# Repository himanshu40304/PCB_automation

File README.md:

# PCB Automation & Design Pipeline

An autonomous, end-to-end PCB design, verification, and manufacturing pipeline powered by **KiCad 10**, **SPICE**, **OpenEMS 3D FDTD**, **ParaView**, and **AI-driven Automation Agents**.

⭐ **If you find this repository useful for your PCB workflows or research, please consider giving it a star!**

---

## 🚀 Overview & Automation Architecture

This repository contains automated workflows, design tools, and complete hardware projects demonstrating AI-assisted schematic creation, SPICE verification, electrical rules check (ERC), automated component placement, routing, clearance isolation, and design rules check (DRC).

```mermaid
graph LR
    A["Requirements & Spec"] --> B["Schematic Capture"]
    B --> C["SPICE Simulation & ERC"]
    C --> D["Board Setup & Constraints"]
    D --> E["Component Placement & Floorplanning"]
    E --> F["Routing & Isolated Plane Pours"]
    F --> G["DRC & DFM Production Audit"]
    G --> H["Manufacturing Gerber & BOM Export"]
```

---

## 📂 Projects in this Repository

### 1. `projects/ACtoDCtoMicrocontroller`
* **Description:** An integrated compact IoT board converting mains AC to regulated 5V & 3.3V DC to power an ESP32/Microcontroller with USB programming, switches, and antenna keepout.
* **Key Features:**
  * **Mains AC Input Stage:** Screw terminal (`J1`), NTC inrush limiter (`RT1`), X-Capacitor (`C1`), and HLK-5M05 isolated AC-DC module.
  * **Microcontroller & Logic Domain:** 3.3V LDO regulator, ESP32 module, reset & boot switches, Micro-USB interface, and dedicated RF Antenna Keep-Out Zone.
  * **Physical Isolation:** Strict primary-to-secondary dielectric isolation barrier.
  * **Artifacts:** Complete `.kicad_sch`, `.kicad_pcb`, interactive SVGs, manufacturing BOM, and CPL files.

#### Visual Showcase & 3D Previews

<p align="center">
  <b>Schematic Diagram (Annotated Subsystems)</b><br>
  
</p>

| Top Layer Layout (HV Isolation & 5V Fill) | Bottom Layer Layout (3.3V & Signal Routing) |
| :---: | :---: |
|  |  |

| Top 3D Assembly (HLK Module & AC Protection) | Bottom 3D Assembly (MCU, Buttons, USB) |
| :---: | :---: |
|  |  |

### 2. `projects/AC_DC_converter_with_regulated_dc`
* **Description:** A **$60\text{ mm} \times 50\text{ mm}$** AC-to-DC Adjustable Regulated Power Supply using a Full-Wave Bridge Rectifier and LM317.
* **Key Features:**
  * **Primary High-Voltage AC Domain ($X \le 120\text{ mm}$):** 2-pin screw terminal (`J1`), MOV surge suppressor (`RV_MOV1`), 5x20mm fuse (`F1`), and 1N4007 bridge rectifier (`D1–D4`).
  * **Secondary Low-Voltage DC Domain ($X \ge 122\text{ mm}$):** $1000\mu\text{F}$ bulk filter (`C1`), LM317 regulator (`U1`), 5k$\Omega$ precision trimpot (`RV1`), output decoupling (`C4`, `C5`), and green LED indicator (`D7`).
  * **Safety & Isolation:** $>3.0\text{ mm}$ physical creepage/clearance barrier between Primary AC and Secondary DC.
  * **Isolated Ground Pours:** Top and Bottom GND copper pours restricted to the DC secondary domain.
  * **Verification Status:** **0 ERC Errors, 0 DRC Errors, 0 Courtyard Overlaps, 0 Boundary Violations**.

#### Visual Showcase & Design Views

| Schematic (Annotated Sections) | 2D PCB Layout (HV/LV Split & GND Pour) |
| :---: | :---: |
|  |  |

<p align="center">
  <b>3D Board Assembly Render</b><br>
  
</p>

### 3. `projects/Binary_Counter_8Bit`
* **Description:** An autonomous 8-Bit Binary Counter circuit ($0 - 255$) featuring an NE555 timer clock generator, 74HC590 8-bit binary counter, 8-LED binary readout bar, speed trimpot, and USB power.
* **Key Features:**
  * **USB-B Micro 5V Input:** Over-current fuse protection (`F1`), Schottky reverse diode (`D1`), and SMAJ5.0A TVS protection (`D2`).
  * **NE555 Precision Clock Generator:** Astable timer circuit with adjustable speed potentiometer (`RV1`) and clock pulse LED indicator (`D_CLK`).
  * **74HC590 8-Bit Binary Counter & Register:** Direct driving of an 8-LED binary output array (`D3 - D10`) with dedicated current limiting resistors (`R3 - R10`).
  * **Active Reset Circuit:** Tactile pushbutton (`SW_RST`) with pull-up resistor (`R_PULL_RST`).

#### Visual Showcase & 3D Previews

<p align="center">
  <b>Schematic Diagram (Timer, Counter & Output Display)</b><br>
  
</p>

| 2D PCB Layout (Floorplan & Traces) | 2D PCB Layout (Copper & Pour View) |
| :---: | :---: |
|  |  |

<p align="center">
  <b>3D Board Assembly Render</b><br>
  
</p>

### 4. `projects/RF_Detector`
* **Description:** A 4-Layer High-Frequency RF Logarithmic Power Detector board ($500\text{ MHz} - 1.0\text{ GHz}$) featuring an SMA edge input, Analog Devices AD8313 logarithmic detector, ADS7042 12-bit SPI ADC, and dedicated analog/digital ground splits.
* **Key Features:**
  * **RF Signal Path:** $50\ \Omega$ microstrip line ($w = 0.38\text{ mm}$) on $0.2\text{ mm}$ FR4 core directly referencing a solid Layer 2 ground plane.
  * **Full-Wave 3D FDTD EM Simulation (OpenEMS):** $S_{11} = -15.96\text{ dB}$ resonance at $750\text{ MHz}$, $-29.66\text{ dB}$ max crosstalk isolation into the adjacent digital SPI bus.
  * **3D Field Visualization (ParaView):** Time-domain wave propagation ($\vec{E}(t)$) and frequency-domain harmonic vector distributions exported as VTK field dumps.

### 5. `projects/RF_LVDS/LVDS` (High-Speed $\ge 400\text{ Mbps}$ Differential Link)
* **Description:** A 4-Layer High-Speed LVDS Evaluation Board featuring **TI SN65LVDS1D (Driver)** and **SN65LVDT2D (Receiver with internal 110 Ω termination)**.
* **Key Features:**
  * **Controlled Impedance Interconnects:** $100\ \Omega$ edge-coupled microstrip ($W = 0.15\text{ mm}, S = 0.15\text{ mm}$) over $0.1\text{ mm}$ prepreg, with $50\ \Omega$ single-ended RF SMA launches.
  * **Ground Integrity & Via Stitching:** 5.0 mm uniform ground stitching grid across the board interior with a perimeter via fence for low-inductance return loops.
  * **3D Full-Wave EM Co-Simulation:** Full FDTD wave propagation ($E$-field, $H$-field, and $J$-current density) animated in ParaView.
  * **Manufacturing:** Complete Gerber RS-274X, NC Drill, and 3D STEP models with 0 DRC violations and 0 unconnected pads.

---

## 🛠️ Automated Tools & Pipeline Frameworks

* **`PCB_AUTOMATION_PIPELINE_GUIDE.md`**: Complete architectural reference guide for automating KiCad schematic capture, layout, SPICE simulation, OpenEMS 3D EM analysis, and Gerber generation.
* **`pcb-workflow.md`**: Step-by-step workflow with mandatory pre-layout SPICE and post-layout OpenEMS verification gates.
* **`KiCAD-MCP-Server`**: Model Context Protocol integration enabling autonomous LLM interaction with KiCad's layout engine.
* **`SPICEBridge` (`kicad-spice`)**: Automated SPICE netlist extraction and ngspice simulation harness.
* **`openems-sim` (`antenna-cad`)**: 3D Full-Wave FDTD Electromagnetic field solver running inside a dedicated Docker container (`antenna-cad-openems`).
* **`ParaView 6.1.1`**: 3D scientific field viewer for near-field coupling, surface currents, and wave propagation animation.
* **`Saturn PCB Toolkit`**: Deterministic analytical transmission line, via capacitance, and thermal modeling toolkit.
* **`Konnect`**: Automated net connectivity and routing optimization toolset.

---

## 🤝 Commercial Inquiries & Custom PCB Design

Need custom hardware design, high-speed differential layout, RF / antenna 3D EM simulation, or pre-fabrication DRC/SPICE auditing?
- Open an issue or start a [GitHub Discussion](https://github.com/himanshu40304/PCB_automation/discussions).
- Turnaround time for SPICE-verified, DRC-clean design packages is typically **under 24–48 hours**.

---

## 📄 License

This project is licensed under the **MIT License** - see the [LICENSE](LICENSE) file for details. Free for both open-source and commercial applications.

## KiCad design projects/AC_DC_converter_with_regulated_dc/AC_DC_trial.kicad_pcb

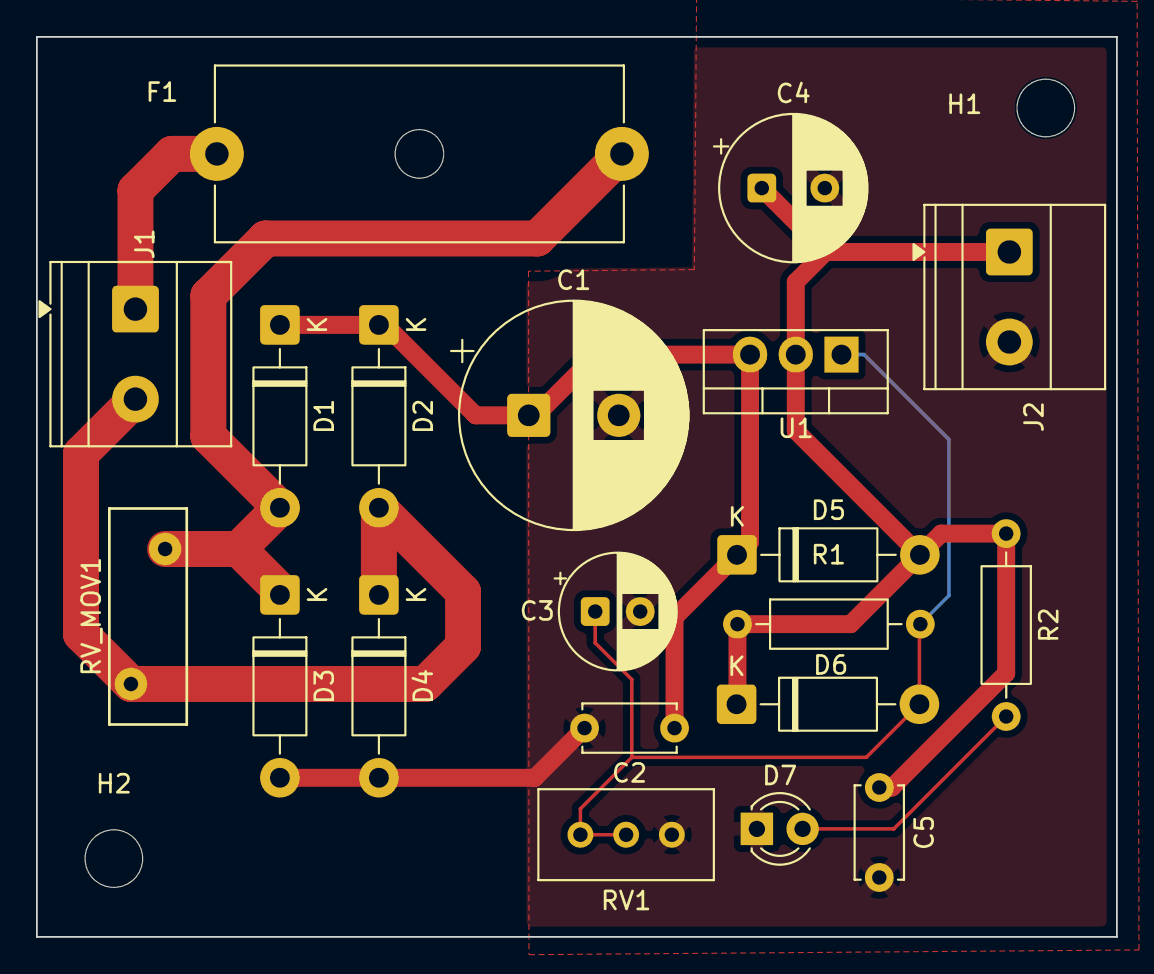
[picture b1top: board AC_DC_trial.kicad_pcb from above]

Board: 4 copper layers, 60.0 x 50.0 mm, 22 parts (0 on the bottom side), 8 nets.

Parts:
C1: 1000uF_50V; CP_Radial_D12.5mm_P5.00mm
C2, C5: 100nF; C_Disc_D5.0mm_W2.5mm_P5.00mm
C3: 10uF_50V; CP_Radial_D6.3mm_P2.50mm
C4: 100uF_50V; CP_Radial_D8.0mm_P3.50mm
D1, D2, D3, D4, D5, D6: 1N4007; D_DO-41_SOD81_P10.16mm_Horizontal
D7: Green_LED; LED_D3.0mm
F1: 1A_250V; Fuseholder_Cylinder-5x20mm_Schurter_0031_8201_Horizontal_Op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
H1, H2: MountingHole_M3; MountingHole_3.2mm_M3
J1: AC_IN; TerminalBlock_Phoenix_MKDS-1,5-2_1x02_P5.00mm_Horizontal
J2: DC_OUT; TerminalBlock_Phoenix_MKDS-1,5-2_1x02_P5.00mm_Horizontal
R1: 240R; R_Axial_DIN0207_L6.3mm_D2.5mm_P10.16mm_Horizontal
R2: 2.2k; R_Axial_DIN0207_L6.3mm_D2.5mm_P10.16mm_Horizontal
RV1: 5k; Potentiometer_Bourns_3296W_Vertical
RV_MOV1: MOV_14D; RV_Disc_D12mm_W4.3mm_P7.5mm
U1: LM317T; TO-220-3_Vertical

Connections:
AC_IN1: F1.1, J1.1
AC_L: D1.2 (A), D3.1 (K), F1.2, RV_MOV1.1
AC_N: D2.2 (A), D4.1 (K), J1.2, RV_MOV1.2
ADJ_NODE: C3.1, D6.2 (A), R1.2, RV1.1, RV1.2, U1.1 (ADJ)
GND: C1.2, C2.2, C3.2, C4.2, C5.2, D3.2 (A), D4.2 (A), D7.1 (K), J2.2, RV1.3
LED_A: D7.2 (A), R2.2
VOUT: C4.1, C5.1, D5.2 (A), D6.1 (K), J2.1, R1.1, R2.1, U1.2 (VO)
VRECT_POS: C1.1, C2.1, D1.1 (K), D2.1 (K), D5.1 (K), U1.3 (VI)

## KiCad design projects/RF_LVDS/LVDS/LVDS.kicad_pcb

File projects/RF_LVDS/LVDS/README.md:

# High-Speed Point-to-Point LVDS Test & Evaluation PCB

A high-speed 4-layer Low-Voltage Differential Signaling (LVDS) evaluation board featuring the **Texas Instruments SN65LVDS1D (Driver)** and **SN65LVDT2D (Receiver with integrated 110 Ω termination)** capable of $\ge 400\text{ Mbps}$ data transmission with co-planar controlled-impedance interconnects, full-coverage ground stitching, and 3D full-wave OpenEMS/ParaView simulation.

---

## 📐 Board Specifications

| Parameter | Specification | Notes |
| :--- | :--- | :--- |
| **Dimensions** | 70.0 mm × 50.0 mm | Standard compact evaluation form factor |
| **Layer Stackup** | 4-Layer Controlled Impedance (JEDEC standard) | $1.6\text{ mm}$ overall thickness, FR4 ($\varepsilon_r = 4.5$) |
| **Layer 1 (Top)** | High-Speed Microstrip + RF SMA Launch | $100\ \Omega$ diff pair ($W=0.15\text{ mm}, S=0.15\text{ mm}$), $50\ \Omega$ single-ended ($W=0.18\text{ mm}$) |
| **Layer 2 (Inner 1)** | Solid Unbroken GND Ground Plane | Continuous reference plane directly under high-speed traces |
| **Layer 3 (Inner 2)** | 3.3V Power Plane (PDN) | Low-impedance power distribution with 100 nF + 1 nF decoupling |
| **Layer 4 (Bottom)** | Solid GND Shield Plane | Ground return reference plane |
| **Via Stitching** | 5.0 mm Interior Grid + 3.5 mm Perimeter Fence | 0.6 mm pad diameter, 0.3 mm drill hole for low-inductance return paths |

---

## ⚡ Circuit Architecture

```mermaid
graph LR
    SMA1["J1: Input SMA (50 Ω)"] -->|"Single-Ended 50 Ω"| U2["TI SN65LVDS1D (Driver)"]
    U2 -->|"/LVDS_P (100 Ω Diff)"| U3["TI SN65LVDT2D (Receiver)"]
    U2 -->|"/LVDS_N (100 Ω Diff)"| U3
    U3 -->|"Single-Ended 50 Ω"| SMA2["J2: Output SMA (50 Ω)"]
    PWR["J3: 3.3V Power Header"] --> DEC["Decoupling (10uF + 100nF + 1nF)"]
    DEC --> U2
    DEC --> U3
```

---

## 🔬 3D Full-Wave Electromagnetic & Field Simulation Pipeline

High-speed PCB signals at $> 400\text{ Mbps}$ are **guided electromagnetic waves**, where energy travels primarily through the dielectric substrate between the signal trace and reference ground plane. 

To validate transmission line dynamics before physical fabrication, this board was simulated using **OpenEMS (Finite-Difference Time-Domain full-wave Maxwell solver)** and visualized in **ParaView 6.1**:

```mermaid
graph LR
    A["KiCad Layout & Stackup"] --> B["OpenEMS 3D FDTD Engine"]
    B --> C["Full-Wave Maxwell Solution (E, H, J fields)"]
    C --> D["ParaView 3D Vector & Surface LIC Analysis"]
```

### Key Simulation Models:
1. **End-to-End Transmission Line Domain (70 mm × 50 mm)**:
   - Full board substrate modeled in FR4 ($\varepsilon_r = 4.5, \tan\delta = 0.02$) over a $0.10\text{ mm}$ prepreg height to Layer 2 solid ground plane.
   - Left SMA input launch ($50\ \Omega$) $\rightarrow$ Driver `U2` $\rightarrow$ $100\ \Omega$ Differential Pair ($W=0.15\text{ mm}, S=0.15\text{ mm}$) $\rightarrow$ Receiver `U3` ($110\ \Omega$ termination) $\rightarrow$ Right SMA output launch ($50\ \Omega$).
2. **Surface LIC (Line Integral Convolution) Vector Field Analysis**:
   - Computes continuous streamflow streaklines directly from the electric vector field $\vec{E}(t)$, revealing:
     - **Radial Launch Pattern**: Coaxial TEM-to-microstrip transition at the SMA connector launch.
     - **Differential Coupling**: Strong transverse field confinement tightly bounded between the positive and negative differential microstrips.
     - **Zero Stray Coupling**: Near-zero field leakage into surrounding ground fill.
3. **Ground Plane Integrity & Perimeter Via Shielding**:
   - High-density ground via stitching matrix (5.0 mm grid) connecting Top, Inner 1, and Bottom ground planes, backed by a perimeter via fence to suppress edge radiation and maintain low-inductance ground return loops.

---

## 🌟 Engineering Benefits of 3D EM Simulation for High-Speed PCBs

| Engineering Challenge | How 3D EM Simulation Resolves It |
| :--- | :--- |
| **Impedance Discontinuities** | Visualizes localized wave reflections and capacitance bumps at SMA launches and chip pad transitions before tape-out. |
| **Differential Symmetry & Skew** | Verifies equal phase velocity and tight coupling between `/LVDS_P` and `/LVDS_N`, preventing common-mode noise conversion. |
| **High-Frequency Return Currents** | Proves that the high-frequency return current stays tightly confined on Layer 2 GND directly beneath the trace path, minimizing loop inductance. |
| **EMI & Edge Radiation Suppression** | Validates that the solid ground reference planes and perimeter stitching fence prevent fringing electromagnetic waves from radiating off the PCB edges. |
| **Pre-Fabrication Signoff** | Eliminates costly PCB prototype respins by diagnosing signal integrity (SI) and electromagnetic compatibility (EMC) bottlenecks in software. |

---

## 📁 Manufacturing Artifacts
- **Gerber RS-274X Package:** `gerber/`
- **Excellon NC Drill:** `gerber/LVDS.drl`
- **3D Mechanical STEP Model:** `LVDS.step`
- **DRC & ERC Status:** **Passed (0 DRC Violations, 0 Unconnected Items)**.

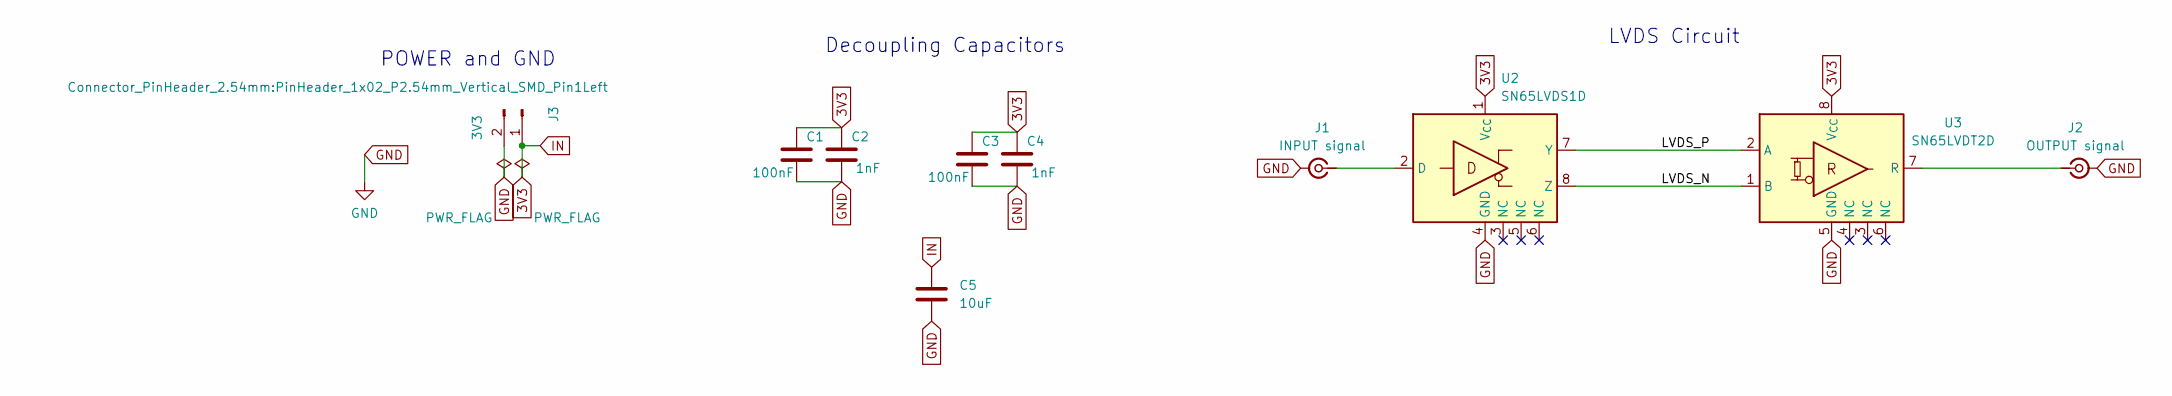
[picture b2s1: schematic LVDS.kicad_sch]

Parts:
C1, C3: 100nF; C_0805_2012Metric
C2, C4: 1nF; C_0805_2012Metric
C5: 10uF; C_0805_2012Metric
J1: INPUT signal; SMA_Amphenol_132134-10_Vertical
J2: OUTPUT signal; SMA_Amphenol_132134-10_Vertical
J3: 3V3; PinHeader_1x02_P2.54mm_Vertical_SMD_Pin1Left
U2: SN65LVDS1D; SOIC-8_3.9x4.9mm_P1.27mm
U3: SN65LVDT2D; SOIC-8_3.9x4.9mm_P1.27mm

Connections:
3V3: C1.1, C2.1, C3.1, C4.1, C5.1, J3.1, U2.1 (V_{CC}), U3.8 (V_{CC})
/LVDS_N: U2.8 (Z), U3.1 (B)
/LVDS_P: U2.7 (Y), U3.2 (A)
GND: C1.2, C2.2, C3.2, C4.2, C5.2, J1.2 (Ext), J2.2 (Ext), J3.2, U2.4 (GND), U3.5 (GND)
unnamed: J1.1 (In), U2.2 (D)
unnamed: J2.1 (In), U3.7 (R)

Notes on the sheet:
LVDS Circuit
Decoupling Capacitors
POWER and GND

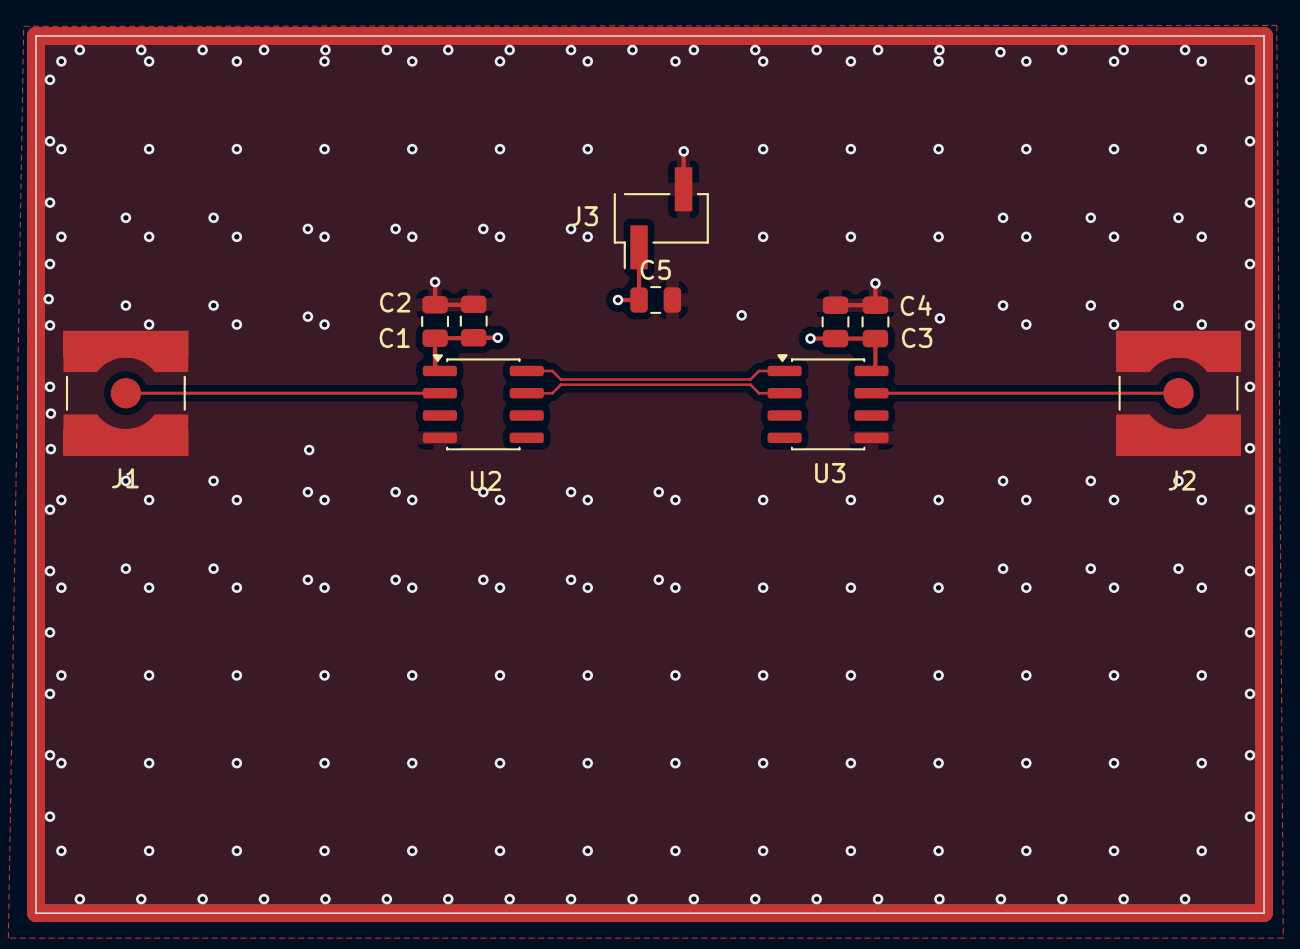
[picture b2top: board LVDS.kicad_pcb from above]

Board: 4 copper layers, 70.0 x 50.0 mm, 10 parts (0 on the bottom side), 6 nets.

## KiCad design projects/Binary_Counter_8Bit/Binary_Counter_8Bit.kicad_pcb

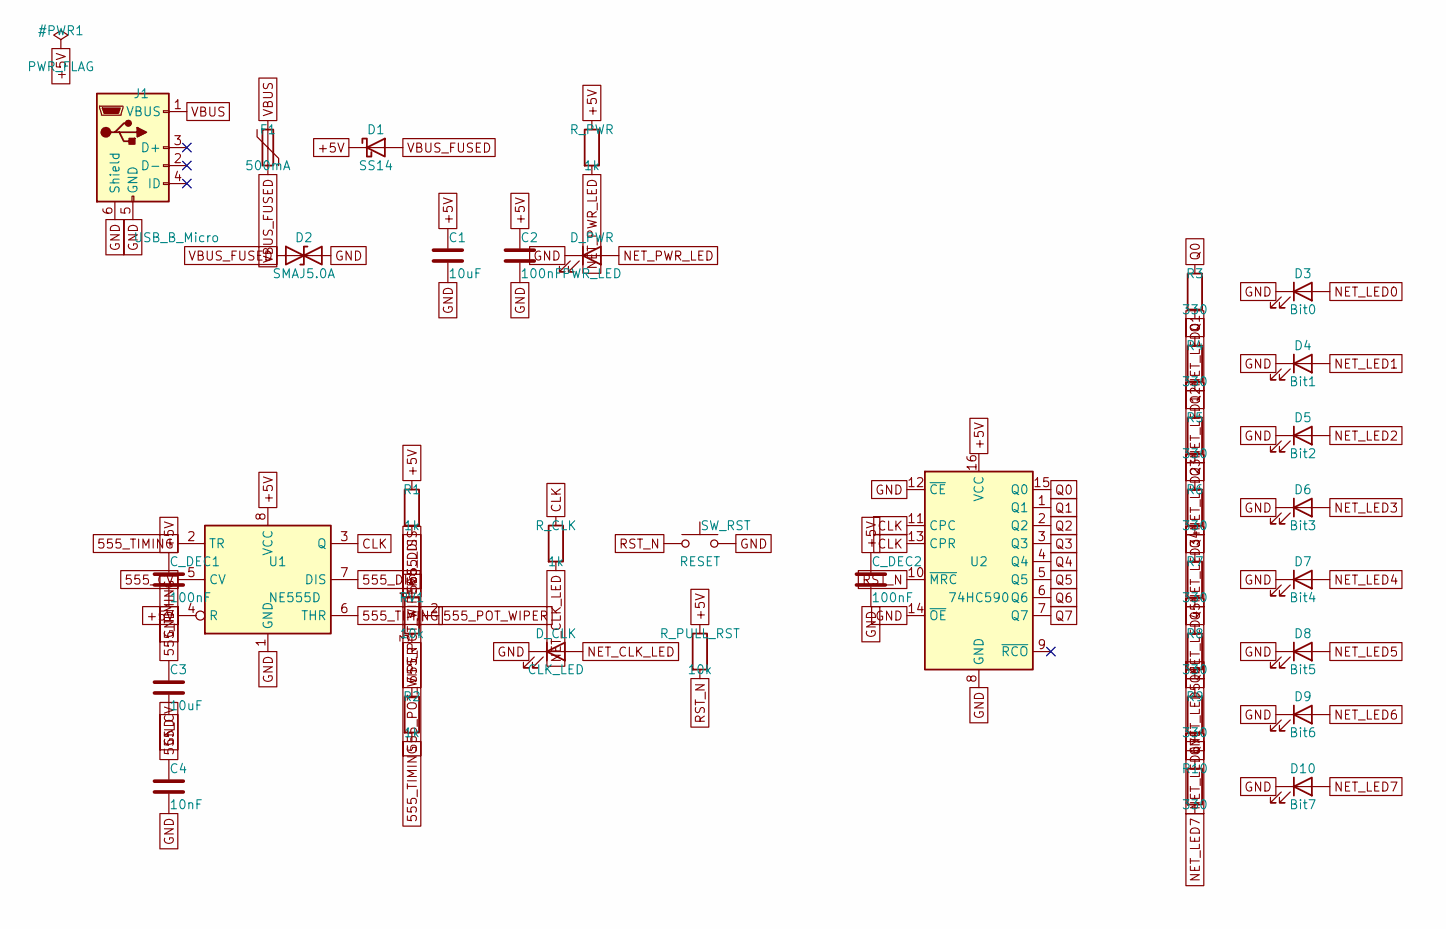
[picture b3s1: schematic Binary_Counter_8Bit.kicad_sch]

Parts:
C1, C3: 10uF; C_1206_3216Metric
C2: 100nF; C_0805_2012Metric
C4: 10nF; C_0805_2012Metric
C_DEC1, C_DEC2: 100nF; C_0805_2012Metric
D1: SS14; D_SMA
D2: SMAJ5.0A; D_SMA
D3: Bit0; LED_0805_2012Metric
D4: Bit1; LED_0805_2012Metric
D5: Bit2; LED_0805_2012Metric
D6: Bit3; LED_0805_2012Metric
D7: Bit4; LED_0805_2012Metric
D8: Bit5; LED_0805_2012Metric
D9: Bit6; LED_0805_2012Metric
D10: Bit7; LED_0805_2012Metric
D_CLK: CLK_LED; LED_0805_2012Metric
D_PWR: PWR_LED; LED_0805_2012Metric
F1: 500mA; Fuse_1206_3216Metric
J1: USB_B_Micro; USB_Micro-B_Molex_47346-0001
R1, R2: 1k; R_0805_2012Metric
R3, R4, R5, R6, R7, R8, R9, R10: 330; R_0805_2012Metric
RV1: 10k; Potentiometer_Bourns_3386P_Vertical
R_CLK: 1k; R_0805_2012Metric
R_PULL_RST: 10k; R_0805_2012Metric
R_PWR: 1k; R_0805_2012Metric
SW_RST: RESET; SW_SPST_PTS645Sx43SMTR92
U1: NE555D; SOIC-8_3.9x4.9mm_P1.27mm
U2: 74HC590; SOIC-16_3.9x9.9mm_P1.27mm

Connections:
555_CV: C4.1, U1.5 (CV)
555_DIS: R1.2, RV1.1, U1.7 (DIS)
555_POT_WIPER: R2.1, RV1.2, RV1.3
555_TIMING: C3.1, R2.2, U1.2 (TR), U1.6 (THR)
+5V: C1.1, C2.1, C_DEC1.1, C_DEC2.1, D1.1 (K), R1.1, R_PULL_RST.1, R_PWR.1, U1.4 (R), U1.8 (VCC), U2.16 (VCC)
CLK: R_CLK.1, U1.3 (Q), U2.11 (CPC), U2.13 (CPR)
GND: C1.2, C2.2, C3.2, C4.2, C_DEC1.2, C_DEC2.2, D2.2 (A2), D3.1 (K), D4.1 (K), D5.1 (K), D6.1 (K), D7.1 (K), D8.1 (K), D9.1 (K), D10.1 (K), D_CLK.1 (K), D_PWR.1 (K), J1.5 (GND), J1.6 (Shield), SW_RST.2, U1.1 (GND), U2.8 (GND), U2.12 (~CE), U2.14 (~OE)
NET_CLK_LED: D_CLK.2 (A), R_CLK.2
NET_LED0: D3.2 (A), R3.2
NET_LED1: D4.2 (A), R4.2
NET_LED2: D5.2 (A), R5.2
NET_LED3: D6.2 (A), R6.2
NET_LED4: D7.2 (A), R7.2
NET_LED5: D8.2 (A), R8.2
NET_LED6: D9.2 (A), R9.2
NET_LED7: D10.2 (A), R10.2
NET_PWR_LED: D_PWR.2 (A), R_PWR.2
Q0: R3.1, U2.15 (Q0)
Q1: R4.1, U2.1 (Q1)
Q2: R5.1, U2.2 (Q2)
Q3: R6.1, U2.3 (Q3)
Q4: R7.1, U2.4 (Q4)
Q5: R8.1, U2.5 (Q5)
Q6: R9.1, U2.6 (Q6)
Q7: R10.1, U2.7 (Q7)
RST_N: R_PULL_RST.2, SW_RST.1, U2.10 (~MRC)
VBUS: F1.1, J1.1 (VBUS)
VBUS_FUSED: D1.2 (A), D2.1 (A1), F1.2

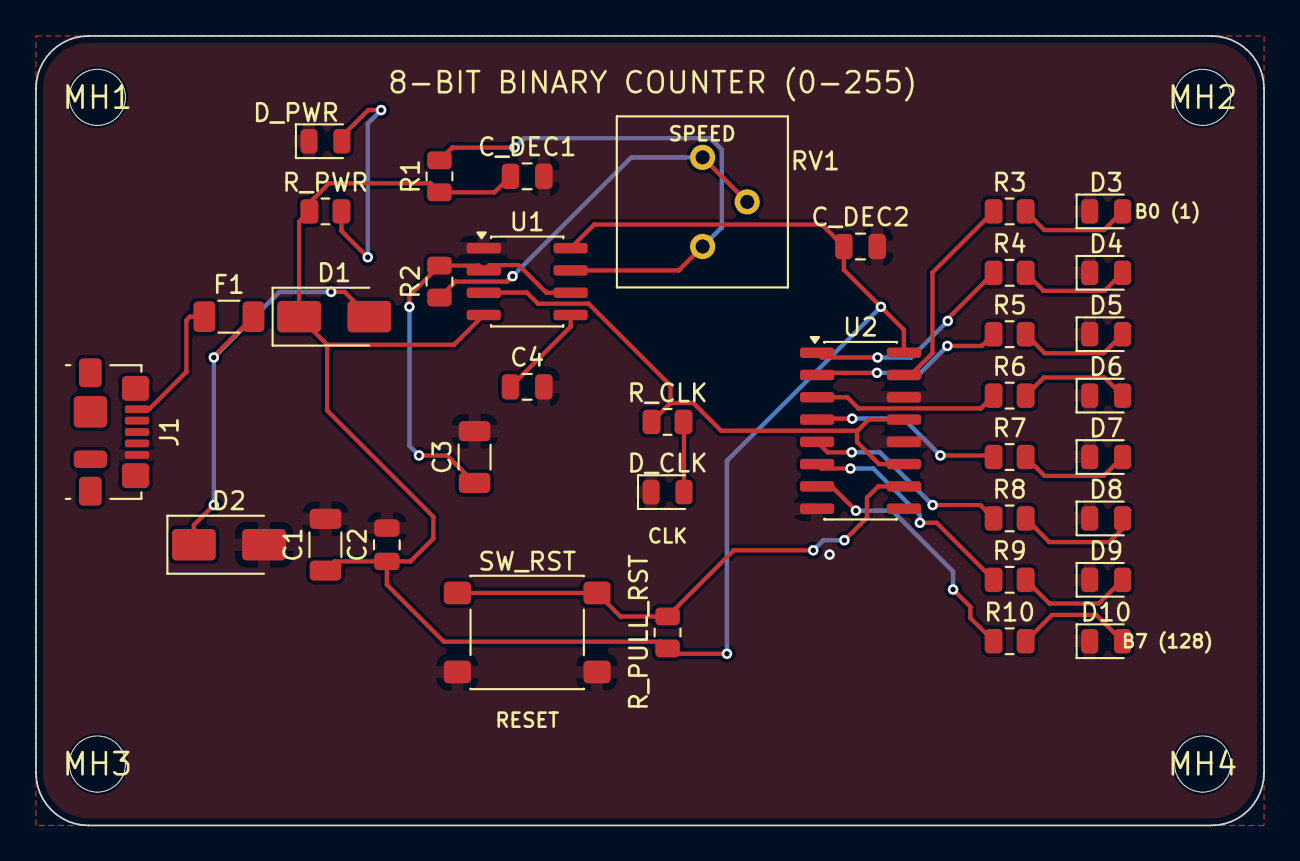
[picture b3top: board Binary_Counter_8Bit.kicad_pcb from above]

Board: 2 copper layers, 70.0 x 45.0 mm, 41 parts (0 on the bottom side), 28 nets.

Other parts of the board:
MH1, MH2, MH3, MH4: MountingHole_3.2mm

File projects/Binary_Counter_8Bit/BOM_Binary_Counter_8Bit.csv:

value,footprint,quantity,references
MountingHole_3.2mm,MountingHole:MountingHole_3.2mm,4,"['MH4', 'MH3', 'MH2', 'MH1']"
USB_B_Micro,Connector_USB:USB_Micro-B_Molex_47346-0001,1,['J1']
330,Resistor_SMD:R_0805_2012Metric,8,"['R7', 'R4', 'R3', 'R8', 'R9', 'R5', 'R6', 'R10']"
SMAJ5.0A,Diode_SMD:D_SMA,1,['D2']
10k,Potentiometer_THT:Potentiometer_Bourns_3386P_Vertical,1,['RV1']
10uF,Capacitor_SMD:C_1206_3216Metric,2,"['C3', 'C1']"
Bit2,LED_SMD:LED_0805_2012Metric,1,['D5']
10nF,Capacitor_SMD:C_0805_2012Metric,1,['C4']
1k,Resistor_SMD:R_0805_2012Metric,4,"['R1', 'R2', 'R_PWR', 'R_CLK']"
RESET,Button_Switch_SMD:SW_SPST_PTS645Sx43SMTR92,1,['SW_RST']
Bit4,LED_SMD:LED_0805_2012Metric,1,['D7']
Bit6,LED_SMD:LED_0805_2012Metric,1,['D9']
Bit1,LED_SMD:LED_0805_2012Metric,1,['D4']
PWR_LED,LED_SMD:LED_0805_2012Metric,1,['D_PWR']
NE555D,Package_SO:SOIC-8_3.9x4.9mm_P1.27mm,1,['U1']
Bit5,LED_SMD:LED_0805_2012Metric,1,['D8']
500mA,Fuse:Fuse_1206_3216Metric,1,['F1']
10k,Resistor_SMD:R_0805_2012Metric,1,['R_PULL_RST']
CLK_LED,LED_SMD:LED_0805_2012Metric,1,['D_CLK']
Bit3,LED_SMD:LED_0805_2012Metric,1,['D6']
100nF,Capacitor_SMD:C_0805_2012Metric,3,"['C2', 'C_DEC2', 'C_DEC1']"
SS14,Diode_SMD:D_SMA,1,['D1']
74HC590,Package_SO:SOIC-16_3.9x9.9mm_P1.27mm,1,['U2']
Bit0,LED_SMD:LED_0805_2012Metric,1,['D3']
Bit7,LED_SMD:LED_0805_2012Metric,1,['D10']

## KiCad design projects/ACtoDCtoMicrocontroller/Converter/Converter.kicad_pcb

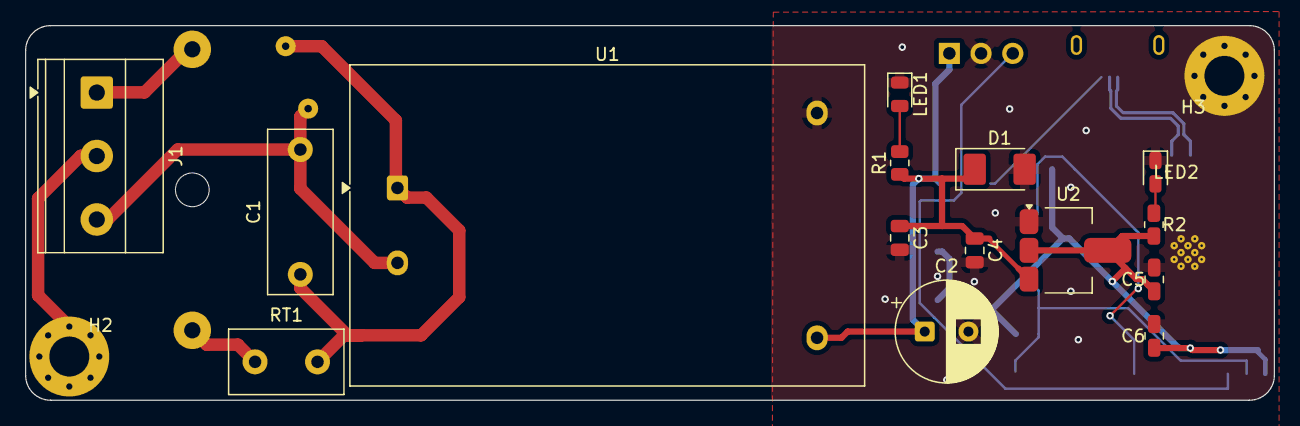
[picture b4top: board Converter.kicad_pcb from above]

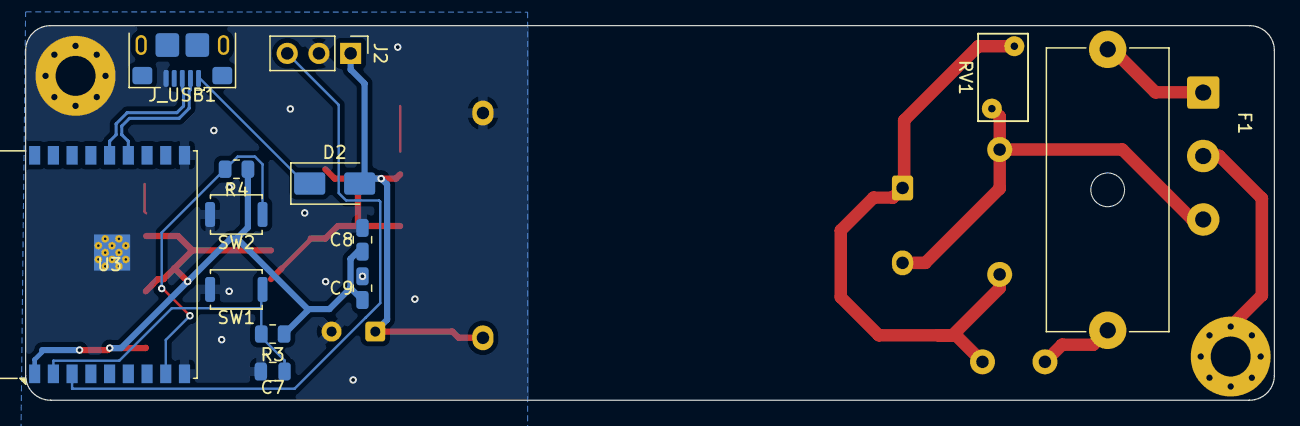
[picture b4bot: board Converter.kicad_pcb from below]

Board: 2 copper layers, 100.0 x 30.0 mm, 30 parts (13 on the bottom side), 16 nets.

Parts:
C1: 100nF 275VAC; C_Rect_L13.0mm_W5.0mm_P10.00mm_FKS3_FKP3_MKS4
C2: 470uF 16V; CP_Radial_D8.0mm_P3.50mm
C3, C6, C7, C9: 100nF; C_0805_2012Metric
C4, C8: 10uF; C_0805_2012Metric
C5: 22uF; C_0805_2012Metric
D1, D2: SS34; D_SMA
F1: 1A 250V; Fuseholder_Cylinder-5x20mm_Schurter_0031_8201_Horizontal_Op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
H2, H3: MountingHole_Pad; MountingHole_3.2mm_M3_Pad_Via
J1: AC_IN (220V); TerminalBlock_Phoenix_MKDS-1,5-3-5.08_1x03_P5.08mm_Horizont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
J2: SERVO_5V (PWM); PinHeader_1x03_P2.54mm_Vertical
J_USB1: USB_B_Micro; USB_Micro-B_Amphenol_10118193-0001LF_Horizontal
LED1: GREEN (5V); LED_0805_2012Metric
LED2: BLUE (3.3V); LED_0805_2012Metric
R1, R2: 1k; R_0805_2012Metric
R3, R4: 10k; R_0805_2012Metric
RT1: 5D-9; C_Disc_D9.0mm_W5.0mm_P5.00mm
RV1: 07D471K; RV_Disc_D7mm_W4mm_P5mm
SW1: RESET; SW_Push_SPST_NO_Alps_SKRK
SW2: BOOT; SW_Push_SPST_NO_Alps_SKRK
U1: HLK-5M05; Converter_ACDC_Hi-Link_HLK-5Mxx
U2: AMS1117-3.3; SOT-223-3_TabPin2
U3: ESP32-C3-WROOM-02

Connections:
/+3.3V: C5.1, C6.1, C8.1, C9.1, R2.1, R3.1, R4.1, U2.2 (VO), U3.1 (3V3)
/+5V: C2.1, C3.1, C4.1, D1.1 (K), D2.2 (A), J2.1, R1.1, U1.4 (+Vout), U2.3 (VI)
/AC_L: C1.1, RT1.2, RV1.1, U1.1 (AC/L)
/AC_L_FUSED: F1.2, RT1.1
/AC_L_IN: F1.1, J1.1
/AC_N: C1.2, J1.3, RV1.2, U1.2 (AC/N)
/EARTH: H2.1 (1_1), J1.2
/GND: C2.2, C3.2, C4.2, C5.2, C6.2, C7.2, C8.2, C9.2, D1.2 (A), H3.1 (1_1), J2.2, J_USB1.5 (GND), LED1.1 (K), LED2.1 (K), SW1.2, SW2.2, U1.3 (-Vout), U2.1 (GND), U3.9 (GND), U3.10 (IO10), U3.19 (GND)
/NET_EN: C7.1, R3.2, SW1.1, U3.2 (EN)
/NET_IO9: R4.2, SW2.1, U3.8 (IO9)
/NET_LED1: LED1.2 (A), R1.2
/NET_LED2: LED2.2 (A), R2.2
/PWM_SERVO: J2.3, U3.3 (IO4)
/USB_D_N: J_USB1.2 (D-), U3.13 (IO18)
/USB_D_P: J_USB1.3 (D+), U3.14 (IO19)
/VBUS: D2.1 (K), J_USB1.1 (VBUS)

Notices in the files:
README.md:
License: MIT
